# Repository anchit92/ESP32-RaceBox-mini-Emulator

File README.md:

# Open Source RaceBox Mini Emulator
> **Disclaimer:** This project is independent and open-source. It is not affiliated with, endorsed by, or officially connected to RaceBox. The name “RaceBox Mini” is used only to describe compatibility.

## Overview

This project provides firmware for an ESP32-based device that acts as a high-performance GPS/IMU Bluetooth Low Energy (BLE) broadcaster. It integrates a U-blox GNSS module for precise position, velocity, and timing data at 25Hz, along with an MPU6050 accelerometer and gyroscope for motion sensing.

The device is designed to be housed in a custom 3D-printed enclosure, with design files included in this repository.

---

> [!TIP]
> **Other Hardware Options**  
> Check Out The [Mods Folder](./Mods) For Other Hardware Options.
> For new builds, check out the [PCB version](./Mods/anchit92/PCB_version).

---

## Features

- **High-Resolution GPS Data**: Achieves 25Hz update rate using a U-blox GNSS module.  
- **Multi-Constellation Support**: Leverages GPS, Galileo, GLONASS, and BeiDou for enhanced accuracy and reliability.  
- **Integrated IMU**: Captures 3-axis accelerometer (`±8g`) and 3-axis gyroscope (`±500 deg/s`) data from the MPU6050.  
- **Real-time BLE Streaming**: Transmits a custom 88-byte data packet containing comprehensive GNSS and IMU information over BLE.  
- **Automatic Configuration**: Robust GPS initialization.
- **Custom RaceBox Protocol**: Data is encapsulated in a UBX-like custom protocol for efficient transmission.  
- **3D Printable Enclosure**: Includes design files for a compact and protective case.  

---

## Bill of Materials (BOM)

To build this project, you'll need the following components:

- **ESP32 Development Board**: (https://a.co/d/fTThpTl)  
- **U-blox GNSS Module**: 
  * MG-902 - https://a.co/d/b6DcUS6 
  * SAM-M10Q - https://a.co/d/54zrba3
  * MG-903 - https://a.co/d/fxp2tLk 
  * HGLRC M100-5883 - https://a.co/d/47V0TqJ
  * AERO SELFIE M10G-5883L- https://a.co/d/cmYLjBP (Theoretically works but I dont have it)
    
  Any M10 based U-blox modules should work, the output rate may vary but you should be able to get 25hz with just GPS enabled. But YMMV.
  
- **MPU6050 Accelerometer/Gyroscope Module**: (https://a.co/d/dCMwffg or similar)  
- **24AWG Hook-up Wire/Jumper Wires** or just use the wiring that comes with GNSS module, its perfect for this application.
- **M3x6 Screws** (2)    
- **Soldering Iron & Solder**
- **USB-C or Micro-USB Cable** (Depending on your ESP32 board, But USB-C all the things)  
- **3D Printer & ABS Filament**  

The electronics should cost under 40$. 

---

## Assembly Instructions

### Wire the Components, load the firmware and test them outdoors.

**ESP32 <--> U-blox GNSS Module:**
- ESP32 GPIO 16 (RX2) <--> GNSS TX  
- ESP32 GPIO 17 (TX2) <--> GNSS RX  
- ESP32 5V or 3.3V <--> GNSS VCC *(check voltage requirements)*  
- ESP32 GND <--> GNSS GND  

**ESP32 <--> MPU6050:**
- ESP32 GPIO 21 (SDA) <--> MPU6050 SDA  
- ESP32 GPIO 22 (SCL) <--> MPU6050 SCL  
- ESP32 5V or 3.3V <--> MPU6050 VCC *(check voltage requirements)*
- ESP32 GND <--> MPU6050 GND  

---

### Prepare the 3D Printed Case

- You shouldn't need any post processing of the printed parts but make sure the buttons slide smoothly in the holes in the lid

### Enclose the Electronics

- Mount the MPU6050 module using M3 screws

- Place the ESP32 in the slot  
- Route cables neatly

- Close the case carefully, it should click together. Make sure none of the wires are pinched or in the way of the buttons

---

## Firmware Setup and Upload

### 1. Install Arduino IDE

Download from the [official Arduino website](https://www.arduino.cc/en/software).

### 2. Install ESP32 Board Support

- Open Arduino IDE Preferences  
- In “Additional Board Manager URLs” add: 
    - https://raw.githubusercontent.com/espressif/arduino-esp32/gh-pages/package_esp32_index.json

### 3. Install Libraries:
- Go to Sketch > Include Library > Manage Libraries... and install the following:
    - Adafruit MPU6050
    - Adafruit Unified Sensor
    - SparkFun u-blox GNSS Arduino Library (ensure it's version 2)

### 4. Open the Sketch: 
- Open the esp32_racebox_mini_emulator.ino in the Arduino IDE.
    - Configure Board Settings:
    - Go to Tools > Board and select your specific ESP32 board (e.g., "ESP32 Dev Module").
    - Ensure the correct Upload Speed and Port are selected.

### 5. Configure Firmware

* Update the GNSS constellations to use(lines 26-31).
  * For the SAM-M10Q module, I recommend using GPS and one local one, Galilieo should work great in most places. Selecting too many constellations can cause the update frequency to drop from 25Hz.
  * For the MG-902 module, you can select up to 4 constellations but it doesnt really make it more accurate than the SAM-M10Q module, but it doesnt appear to drop its frequency either, so might as well.

  https://app.qzss.go.jp/GNSSView/gnssview.html This could help you pick which constellations to pick.

* **OPTIONAL** – You may update the **10-digit number** in the `deviceName` on **line 33** to personalize your device.

    * **ID Limit:** If you intend to use this with the RaceBox App, The number must be **less than 4000000000**. The RaceBox app will not connect to devices with an ID of 4000000000 or higher.

    * **Prefix Requirement:** Make sure to **keep** the `"RaceBox Mini "` prefix unchanged—only change the numbers.

      ✅ **Correct:**
      `String deviceName = "RaceBox Mini 3999999999";`
    
      ❌ **Incorrect (Prefix changed):**
      `String deviceName = "MY GPS 6942069420";`
    
      ❌ **Incorrect (Number too high):**
      `String deviceName = "RaceBox Mini 4000000000";`

### 6. Upload the Firmware

* Click the **Upload** button (the right arrow icon) in the Arduino IDE to compile and upload the code to your ESP32.

  * If upload fails, try this sequence while the output shows "Connecting....":

    1. Hold the **BOOT** button
    2. Press and release the **EN** button
    3. Then release the **BOOT** button

* Open the **Serial Monitor** to verify startup. Initialization is complete when you see:

  BLE Packet Rate: 0.00 Hz | GNSS Update Rate: 25.00 Hz

  printed every 5 seconds.

## 3D Printed Enclosure

The repository includes `*.3mf` files for the custom 3D-printed enclosure designed specifically for the components in the BOM.

* 1x Base file.(either the GoPro mount version or the basic one to use with velcro)
* 1x Lid depending on the the type of GPS module you have.
* 2x Buttons (If you print a lid that supports buttons)
* 1x axdl_mount

Theres a Accelerometer blank included if you have a different accelerometer to create your own mount.

### Recommended Print Settings:

* **Material:** ABS (for durability and heat resistance, especially if used in a car)
* **Layer Height:** 0.2mm
* **Infill:** 15-20% (for sufficient strength)
* **Nozzle Temperature:** (Refer to your filament manufacturer's recommendations)
* **Bed Temperature:** (Refer to your filament manufacturer's recommendations)

## Usage

Once the firmware is uploaded and the device is powered on:

1.  The ESP32 will start advertising a BLE service named "**RaceBox Mini 0123456789**"(the devicename you customized before uploading the firmware).
2.  Use a compatible BLE client application to connect to the device.
    - Tested compatible apps, theoretically anything that supports a racebox mini should work.
        - Solostorm (Android)
        - RaceChrono (Android)
        - RaceChrono Pro (Android/iOS)
        - NMEAconnect (iOS)
        - AutoX DL(iOS)
        - Racebox App (Android/iOS)

## Contribution

Feel free to open issues or submit pull requests if you have suggestions, improvements, or bug fixes.

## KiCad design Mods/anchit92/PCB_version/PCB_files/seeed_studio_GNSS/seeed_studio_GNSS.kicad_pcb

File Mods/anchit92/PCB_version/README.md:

# RaceBox Mini Emulator - Custom PCB Version

[← Back to Main Repository](../../../)

## Overview

An open-source custom PCB and firmware project for a low-power, high-performance RaceBox Mini Emulator. 

**Why this version?** I created this custom PCB to learn PCB design, while standardizing on a single, reliable GNSS module (u-blox SAM-M10Q) and IMU (LSM6DS3) for better optimization and consistency across builds.

---

## Features

- **25Hz GNSS Data**: High-precision positioning using the u-blox SAM-M10Q module.
- **Integrated IMU**: Uses the onboard 6-axis IMU (LSM6DS3) of the XIAO Sense for "Shake-to-Wake" functionality.
- **Battery Powered**: Integrated battery charging and monitoring natively supported by the XIAO.
- **Ultra-Low Power Optimization**: Refined sleep modes achieving a ~40µA deep sleep baseline.
- **BLE Streaming**: Emulates the custom RaceBox protocol identically.
- **Custom PCB Integration**: Minimizes wiring and footprint size for a clean, stable build.

---

## Bill of Materials (BOM)

- **Microcontroller**: [Seeed Studio XIAO nRF52840 Sense](https://www.digikey.com/en/products/detail/seeed-technology-co-ltd/102010469/16652896)
- **GNSS Module**: [u-blox SAM-M10Q-00B](https://www.digikey.com/en/products/detail/u-blox/SAM-M10Q-00B/16672678)
- **Battery**: [1S 400mAh LiPo Battery](https://www.digikey.com/en/products/detail/adafruit-industries-llc/3898/9685336)
  - *Alternatively*, any LiPo battery up to 10mm tall, 25mm wide, and 40mm long should fit in the space in the case. (e.g., [Amazon Option](https://www.amazon.com/dp/B09F9VK77V?ref=ppx_yo2ov_dt_b_fed_asin_title))
  -*Alternatively* Search and pick a 802540 or 102540(untested) battery. They should all fit.
- **PCB**: [JLCPCB](https://www.jlcpcb.com/)
- **M3 Screw**: 1x M3 BHCS 4-6mm (for the pcb)
- **3D Printed Case**: Custom 3D printed case compatible with the PCB footprint.(you can get these manufactured at jlcpcb too, but I haven't tried that service from them)

Approximate Cost : $60

---

## PCB Manufacture

Use the fabrication files in `PCB_files/seeed_studio_GNSS/jlcpcb/production_files/` to order your assembled boards. 
- **Assembly Type**: Order all of them with "Economic" assembly on the **top side only** (the cost to do 2 or 5 is basically the same so dont bother skimping out).
- **Files**: The BOM file and the CPL file are included in the production files folder. 
- *Note: It should cost something like $7-$10 shipped for 5 boards. If the fabrication app quotes something like $40, it may be bugged—try refreshing or re-uploading the files.*

---

## Assembly & Wiring
If you order your PCB with JLCPCB SMT Assembly, note that having them include and solder the SAM-M10Q GNSS module is far too expensive. 

Therefore, **the board is specifically designed so that you can easily solder the GNSS module by hand**. You will need to:
1. Solder the **u-blox SAM-M10Q** GNSS module onto its designated footprint on the PCB. Note the orientation in the picture.
   - Align the package on the PCB.
   - Start with a single pin in one corner and fix it to the board. Then make sure it’s still aligned properly and do the same on the opposite corner.
   - Lots of flux all around, optionally use leaded solder to make this easier, then drag solder and inspect your joints, more flux and reflow as needed until you have no bridges and good joints on all the pins.
2. Solder the **Seeed Studio XIAO nRF52840 Sense** directly to the designated pads on the PCB using castellated mounting.

3. Solder the LiPo battery to the battery pads on the bottom of the XIAO.
4. Secure the battery to the case with double-sided tape/foam strips to prevent it from rattling around and snap the assembly together.

> [!NOTE]
> **Optional: V_BKP Cuttable Trace (Back of the board, v1.1+)**
> There is a `V_BKP` cuttable trace on the back of the custom PCB. **It is connected by default in v1.1**, keeping the GNSS module's backup RAM powered during sleep for a faster lock on wake-up.
> - **Connected (default):** Significantly faster GNSS lock times (reduces lock time from ~40 seconds down to ~10 seconds). Increases Light Sleep current from ~15µA up to 40-50µA.
> - **Cut:** Drops Light Sleep current back down to ~15µA at the cost of slower initial GNSS lock times.
> **Recommendation:** *Leave it connected.* Even with the larger ~50µA continuous draw, the device will effortlessly sit in standby for many months. The massive improvement in initial GPS lock times almost always outweighs holding onto extreme long-term battery life.

---

## Firmware Setup

### 1. Install Board Support
1.  Open Arduino IDE Preferences.
2.  Add `https://files.seeedstudio.com/arduino/package_seeeduino_boards_index.json` to "Additional Board Manager URLs".
3.  Go to **Tools > Board > Boards Manager**.
4.  Search for "Seeed nRF52" and install **Seeed nRF52 Boards**.
5.  Select **Seeed XIAO nRF52840 Sense** as your board.

### 2. Install Libraries
Install the following libraries via the Arduino Library Manager:
- **Seeed Arduino LSM6DS3** (for the onboard IMU)
- **SparkFun u-blox GNSS Arduino Library** (Version 2.x)
- **Adafruit TinyUSB**

### 3. Upload
1. **Confirm Soldering of SAM-M10Q**: After soldering the SAM-M10Q to the PCB, confirm that it is properly connected by loading the `GNSS_Debug_Passthrough/` sketch and checking for the output of NMEA sentences on the serial monitor.
2. **Burn OTP Settings**: Flash the `Code/M10_OTP_Burner/M10_OTP_Burner.ino` sketch to the nRF52840 to write the precise configurations to the SAM-M10Q (required for persistent 115200 baud communication across hardware reboots without battery backup and high performance mode for 25hz GNSS data).
3. **Flash Main Firmware**: Open `Code/nRF52840_racebox_mini_emulator_always_on/nRF52840_racebox_mini_emulator_always_on.ino` and upload it to your board to begin using it.
   - *Hardware Note:* The software logic natively handles the custom PCB requirements, such as inverse logic for the `GPS_EN_PIN` (pull LOW to enable) and optimal deep-power-down states. Ensure `#define PCB_VERSION` is uncommented in the `.ino` file if using this specific PCB.

---

## Customization

You can customize the firmware by modifying the `#define` lines at the top of the `.ino` file:

### 1. GNSS Constellations
Select which satellite systems to use. More systems = faster/better fix but slightly higher power usage and lower Refresh Rate.
```cpp
#define ENABLE_GNSS_GPS      // Always keep GPS enable
#define ENABLE_GNSS_GALILEO  // Recommended for best performance
// #define ENABLE_GNSS_GLONASS // Optional
// #define ENABLE_GNSS_BEIDOU  // Optional
```

### 2. Device Name
Personalize the BLE broadcast name (keep the "RaceBox Mini " prefix).
```cpp
#define SERIAL_NUM "0123456789" // The unique 10-digit serial
```

### 3. Sleep Timeout
Adjust how long the device waits before entering Light sleep after disconnection (default: 10 minutes).
```cpp
#define GPS_HOT_TIMEOUT_MS 900000 // 15 Minutes (Stay powered after disconnect)
```

### 4. Charging Behavior
Configure whether the device sleeps or stays active while charging.
```cpp
#define SLEEP_WHILE_CHARGING true // true = Efficiency (Sleeps), false = Performance (Always Active)
```

---

## Power Consumption & Runtime

- **Active Mode**: ~20mA - 40mA depending on fix / constellations.
- **Light Sleep** (BLE Advertising, GNSS Off): ~15µA (V_BKP cut) to 40-50µA (V_BKP connected, default)
  - Available in 'Always On' firmware / Configurable.
  - Default behavior for the PCB Version.
- **Deep Sleep** (System OFF, Wake-on-Shake): ~10µA - 40µA
  - *Theoretical Shelf Life*: >1 Year.

> [!NOTE]
> **LiPo Battery Caveats**:
> While the theoretical sleep runtime is years, real-world battery life is limited by:
> 1.  **Self-Discharge**: LiPo batteries lose ~2-5% of their charge per month even when disconnected.
> 2.  **Protection Circuit**: The battery's internal BMS consumes a small amount of power (2-10µA).
> 3.  **Temperature**: Extreme cold or heat significantly reduces effective capacity.
> 
> *Expect practically ~6-12 months of standby time in Deep Sleep.*

---

## Power Modes & Wake Functionality

This device supports two power-saving modes depending on the Configuration in the `.ino` file.

### 1. Light Sleep (Default Configuration)
**Behavior**: GNSS and IMU are powered down, but **BLE Advertising continues** (at a slower Eco rate).
**Usage**: Recommended for most users. Ensures the device is always discoverable and ready to connect instantly.
**Power**: ~15µA to ~50µA (depending on V_BKP cuttable trace). Both configurations offer amazing standby life. Theoretical standby on a standard 400mAh battery:
- **V_BKP cut (~15µA)**: ~1,111 days (~3 years)
- **V_BKP connected (~40-50µA, default in v1.1+)**: ~333 to ~416 days (~11-14 months)
*(Note: Real-world results will be lower due to battery self-discharge and BMS overhead, but in both cases, you will easily achieve many months of standby. **Leaving V_BKP connected is highly recommended** since ~11 months is more than enough time for most practical uses, and the vastly improved lock times are worth it.)*

**Trigger**:
- Occurs after GPS Hot Timeout after BLE disconnection. (default 15 minutes)

### 2. Deep Sleep (Optional Configuration)
**Behavior**: The device turns OFF completely (No BLE, No GNSS).
**Usage**: For extreme long-term storage where no BLE broadcast is desired.
**Configuration**:
- Enable by setting `#define ENABLE_DEEP_SLEEP true` in the firmware.
- Adjust `DEEP_SLEEP_DAYS` (default: 1 day) to automatically enter Deep Sleep after extended inactivity.
  
**Wake-Up**:
- **Shake-to-Wake**: The onboard accelerometer detects motion/taps and instantly wakes the device.
- **Plug-to-Wake**: Connecting USB power will also wake the device.

---

## Usage

1.  If using a battery it should always be powered on, If it in deep sleep, shake to to wake it up.
2.  The Blue LED on the XIAO will indicate BLE Connection (named "RaceBox Mini 0123456789" by default).
3.  Connect using a compatible app (RaceChrono, SoloStorm, etc.).
4.  **Charging**: The XIAO handles charging automatically when USB is connected. The green charge LED on the XIAO will light up while charging.
    - **Rate**: Fixed at **100mA**. Charging a dead 400mAh battery takes ~4-5 hours.
5.  The Red and Green LED on the XIAO will indicate the Fix Status of the GNSS Module.
    - Red: No Fix
    - Green: 3D Fix
    - Yellow: 2D Fix

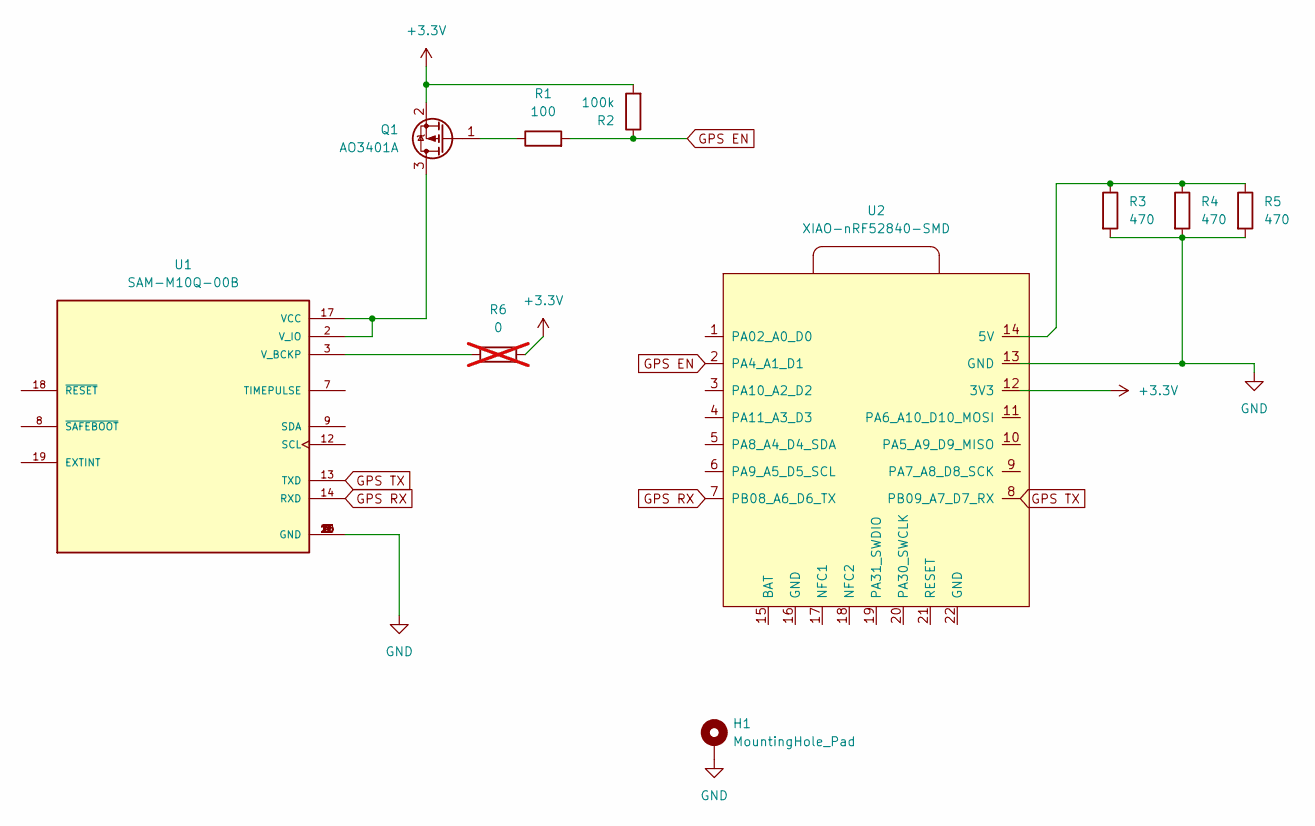
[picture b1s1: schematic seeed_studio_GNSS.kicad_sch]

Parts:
H1: MountingHole_Pad; MountingHole_3.2mm_M3_DIN965_Pad
Q1: AO3401A; SOT-23
R1: 100; R_0603_1608Metric
R2: 100k; R_0603_1608Metric
R3, R4, R5: 470; R_0603_1608Metric
R6: 0; R_0402_1005Metric; not fitted
U1: SAM-M10Q-00B; XCVR_SAM-M10Q-00B; PARTREV R03
U2: XIAO-nRF52840-SMD

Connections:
+3.3V: Q1.2 (S), R2.2, R6.2, U2.12 (3V3); also elsewhere on the board
GND: H1.1, R3.2, R4.2, R5.2, U1.1 (GND), U1.4 (GND), U1.5 (GND), U1.6 (GND), U1.10 (GND), U1.11 (GND), U1.15 (GND), U1.16 (GND), U1.20 (GND), U2.13 (GND)
GPS EN: R1.2, R2.1, U2.2 (PA4_A1_D1)
GPS RX: U1.14 (RXD), U2.7 (PB08_A6_D6_TX)
GPS TX: U1.13 (TXD), U2.8 (PB09_A7_D7_RX)
unnamed 5: R6.1, U1.3 (V_BCKP); also elsewhere on the board
unnamed: Q1.3 (D), U1.2 (V_IO), U1.17 (VCC)
unnamed: Q1.1 (G), R1.1
unnamed: R3.1, R4.1, R5.1, U2.14 (5V)

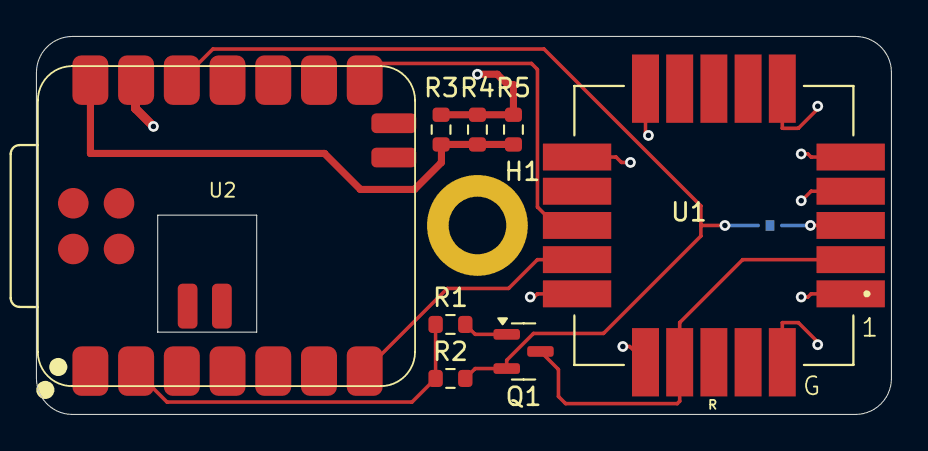
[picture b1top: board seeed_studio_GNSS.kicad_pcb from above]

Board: 2 copper layers, 47.5 x 21.0 mm, 10 parts (1 on the bottom side), 9 nets.

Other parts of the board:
JP1: SolderJumper_2_Bridged; SolderJumper-2_P1.3mm_Bridged_Pad1.0x1.5mm

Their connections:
+3.3V: JP1.2 (B); also elsewhere on the board
unnamed 5: JP1.1 (A); also elsewhere on the board

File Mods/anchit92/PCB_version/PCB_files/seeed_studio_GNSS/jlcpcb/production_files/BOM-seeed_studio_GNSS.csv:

Comment,Designator,Footprint,LCSC,Quantity
100,R1,R_0603_1608Metric,C22775,1
100k,R2,R_0603_1608Metric,C25803,1
470,"R3,R4,R5",R_0603_1608Metric,C23179,3
AO3401A,Q1,SOT-23,C15127,1

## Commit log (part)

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2025-06-12 Update README.md
    Fixed Typos.
2025-06-26 Added moving average for smoothing IMU data
2025-06-28 Improved clearances for printing in PETG/PLA. Still should work well with ABS.
2025-06-29 Fixed base print orientation Added button with more clearance
2025-07-07 No IMU version
2025-07-20 Added no buttons lids
2025-07-20 fix names
2025-07-20 Update README.md
    added note about buttons
2025-07-22 Fixed gnss constellations,Cant just turn them all ON without any negative consequences
2025-07-22 Documentation update, kalman filter on IMU data
2025-07-22 fix spacing
2025-08-20 Update LICENSE
2025-08-22 Added CAD and STL's for 18mm gps antenna modules
2025-08-22 Update esp32_racebox_mini_emulator.ino
    Unintended change.
2026-01-10 Racebox App updates
2026-01-10 Refactor BLE characteristic handling and updates
2026-01-10 Update BLE connection handling and MTU settings
2026-01-10 Replace Kalman filters with Exponential Moving Average
    Removed Kalman filter implementation for accelerometer and gyroscope. Implemented Exponential Moving Average for sensor data filtering.
2026-01-11 Migrate to NimBLE-Arduino
2026-01-11 Update esp32_racebox_mini_emulator.ino
    Cleanup
2026-01-12 Added Slim Base
2026-01-12 Fix print orientation
2026-01-17 Update esp32_racebox_mini_emulator.ino
    Code Cleanup
2026-01-18 Update esp32_racebox_mini_emulator.ino
    Increase delay to prevent choking the BLE stack
2026-01-19 Update esp32_racebox_mini_emulator.ino
    Update accelerometer sampling and smoothing
2026-01-20 Update esp32_racebox_mini_emulator.ino
    Set power to high
2026-01-25 Added code for battery version using a seeed studio XIAO nRF52840 Sense
2026-01-25 Cleanup
2026-01-25 battery reporting fixes
2026-01-26 Update nRF52840_racebox_mini_emulator_always_on.ino
    Battery Management updates
2026-01-27 more LED states, Bettery Battery Reporting. Fix bug with IMU power management
2026-01-27 More Battery management
2026-01-28 More power optimization
2026-01-29 Added Cad and STL and Readme
2026-01-29 Corrected CAD
2026-01-29 corrected print orientation
2026-01-29 Lets try this again
2026-01-29 Prusa slicer wont save files in the correct orientation for me? Cura it is
2026-01-29 correction
2026-01-29 Added LED states
2026-01-29 More details
2026-01-29 ireduce advertizing packet to force name detection
2026-01-29 added support for mpu6500
2026-01-30 Put my new oscilloscope to use
2026-01-30 Trying to squeeze every amp out of this thing
2026-01-30 Minor tweaks
2026-01-30 update documentation
2026-01-30 Improve Reliability
2026-01-31 grammer
2026-01-31 Reporting Tweaks
2026-01-31 Battery% is complicated
2026-01-31 default number
2026-01-31 Typo
2026-01-31 Fixed edge case where if turned on during charging it wont go back to sleep
2026-02-01 Readme updates
2026-02-01 Am i Merging?
2026-02-01 Simplify IMU filterring and use the onboard filters to offload from software
2026-02-02 Update README.md
    Doesnt work, too dirty
2026-02-02 more verbose gps config
2026-02-02 revert unintended change
2026-02-02 i'm dum
2026-02-02 more notes
2026-02-02 update GPS notes
2026-02-03 reorganization
2026-02-03 Corrected base orintation more reorganization added extra gps module lid
2026-02-10 Made mods folder
2026-02-10 correct language
2026-02-10 correct5 descriptio
2026-02-10 hyperlink
2026-02-10 Update SERIAL_NUM to '0123456789'
2026-02-10 fix folder structure
2026-02-10 Update README for RaceBox Mini Emulator Battery Version
2026-02-10 Update README with project details and features
2026-02-12 Remove INPUT_PULLDOWN from pin 11
    Removed INPUT_PULLDOWN mode from pin 11.
2026-02-15 Reset GPS baud rate in power management
2026-02-21 Add else clauses for GNSS enable checks
2026-02-21 Enable SBAS and QZSS GNSS options
2026-03-13 Refactor battery and GPS management for efficiency
    Updated battery management and GPS handling logic. Enhanced power efficiency and added support for no-battery mode.
2026-03-13 Comment out PCB_VERSION definition
    Comment out the PCB_VERSION definition for flexibility.
2026-03-13 added utilities
2026-03-13 Update README.md for RaceBox Mini Emulator
2026-03-14 first commit for PCB version
2026-03-14 set default as pcb version
2026-03-14 fix bad git stuff
2026-03-14 Revise README with new content and clarifications
    Updated README to include additional information about hardware options, assembly instructions, and firmware setup.
2026-03-15 Update 3D printed case description in README
2026-03-15 Update GNSS Constellations section in README
    Clarified the impact of selecting satellite systems on power usage and refresh rate.
2026-03-16 Revise PCB manufacturing instructions in README
    Updated assembly type description and cost estimate for PCB manufacturing.
2026-03-16 Revise README for clarity and additional details
    Updated README to include additional information on hardware options, assembly instructions, and firmware setup.
2026-03-16 Modify startup LED flash count from 5 to 1
    Changed the LED flash indication from 5 times to 1 time during startup.
2026-03-17 Add Ko-fi username for funding support
2026-03-17 Revise battery specifications in README.md
    Updated battery options in README with alternative sizes.
2026-03-20 Update README with project details and instructions
2026-03-22 Clarify GNSS module orientation in assembly instructions
    Added a note about the orientation of the GNSS module during soldering.
2026-03-25 added vented case
2026-03-30 added instructions to solder gps
2026-03-30 Added notes about v_bkp
2026-03-30 update recommendation
2026-04-19 Improve discoverability from sleep, Simplify Battery % reporting.
